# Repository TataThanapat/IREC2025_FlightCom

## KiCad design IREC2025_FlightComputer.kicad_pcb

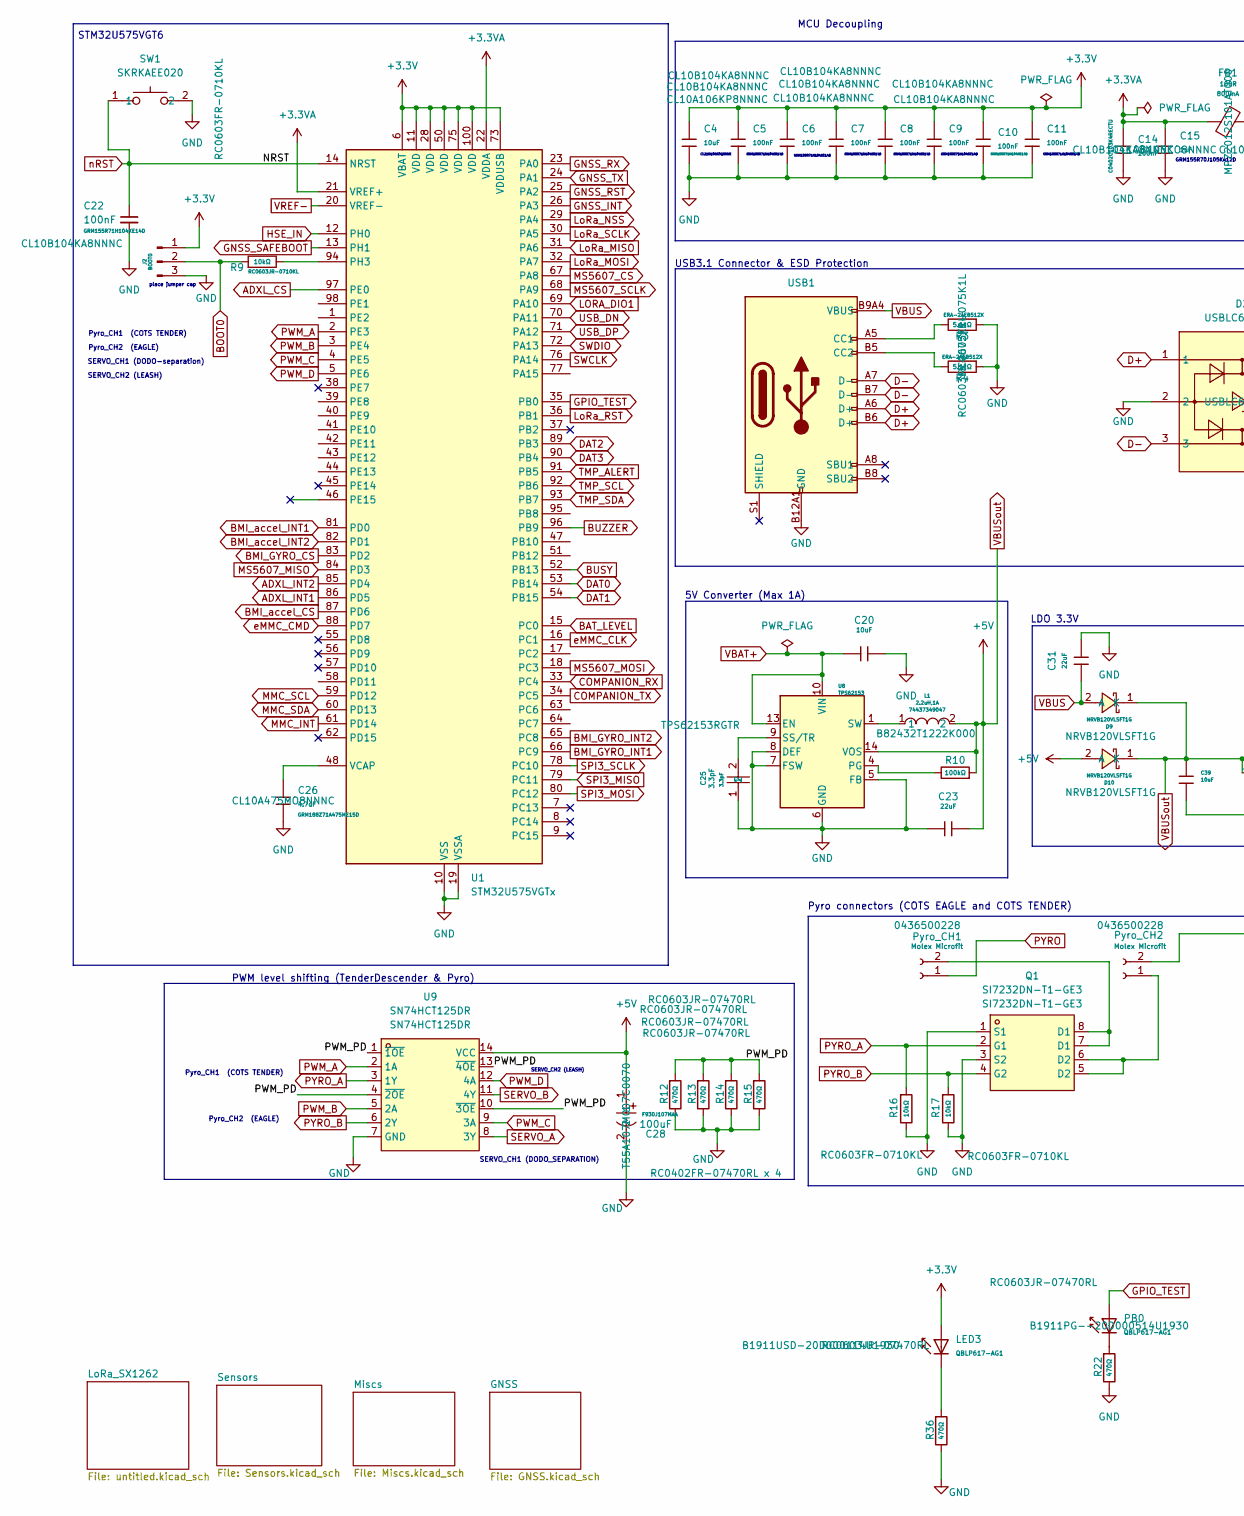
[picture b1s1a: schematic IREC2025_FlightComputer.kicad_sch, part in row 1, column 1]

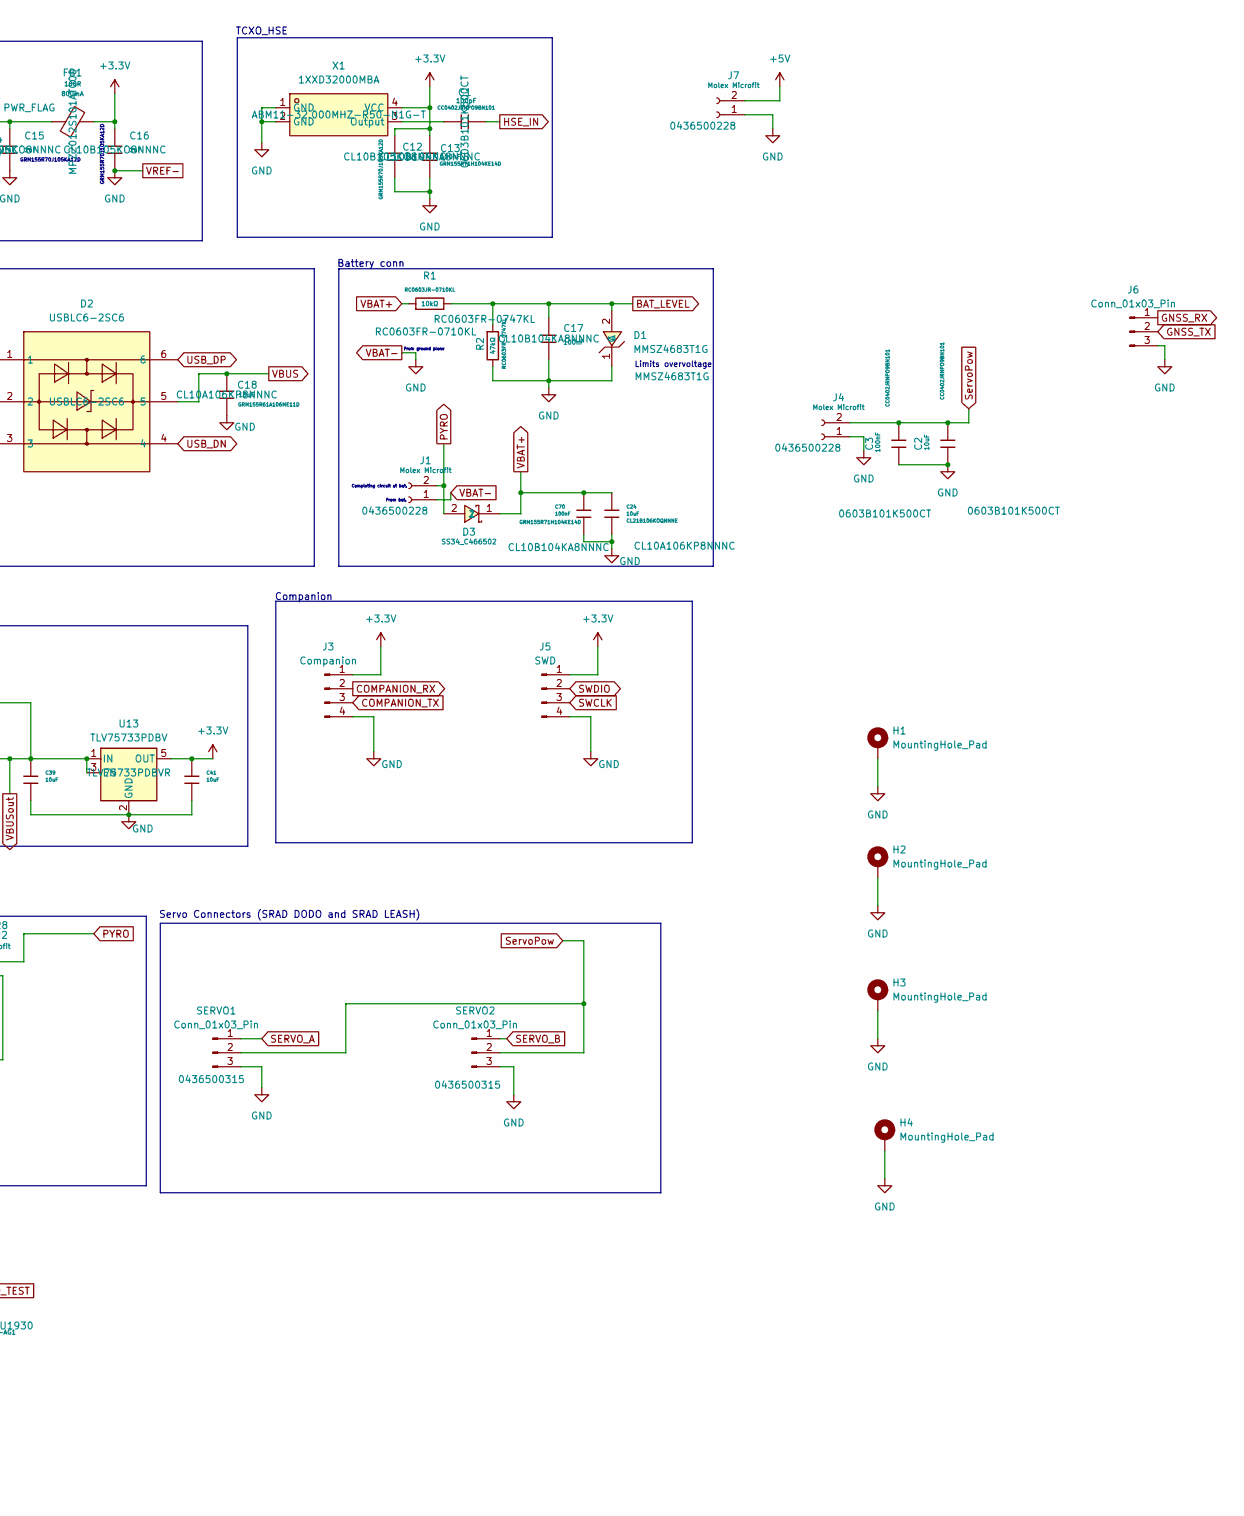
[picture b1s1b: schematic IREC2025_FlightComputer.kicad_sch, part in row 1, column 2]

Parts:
C1: 100pF; C_0603; Voltage Rated 50V; Tolerance ±5%; Part 0402CG101J500NT; LCSC C1546
C2: 10uF; C_0603; Voltage Rated 50V; Tolerance ±5%; Part 0402CG101J500NT; LCSC C1546
C3: 100nF; C_0603; Voltage Rated 50V; Tolerance ±5%; Part 0402CG101J500NT; LCSC C1546
C4, C18: 10uF; C_0603; Voltage Rated 6.3V; Tolerance ±20%; Part CL05A106MQ5NUNC; LCSC C15525
C5, C6, C7, C8, C9, C10, C11, C13, C17: 100nF; C_0603; Voltage Rated 16V; Tolerance ±10%; Part CL05B104KO5NNNC; LCSC C1525
C12, C15, C16: 1uF; C_0603; Voltage Rated 25V; Tolerance ±10%; Part CL05A105KA5NQNC; LCSC C52923
C14: 100nF; C_0603; Voltage Rated 50V; Tolerance ±10%; Part CL05B103KB5NNNC; LCSC C15195
C20: 10uF; C_0603; Voltage Rated 25V; Tolerance ±20%; Part CL10A106MA8NRNC; LCSC C96446
C22: 100nF; C_0603; Digikey Parts CL10B104KA8NNNC
C23, C31: 22uF; C_0603; Voltage Rated 6.3V; Tolerance ±20%; Part CL10A226MQ8NRNC; LCSC C59461
C24, C39, C41: 10uF; C_0603; Voltage Rated 50V; Tolerance ±10%; Part CL31A106KBHNNNE; LCSC C13585
C25: 3.3pF; C_0603; LCSC Part C76906
C26: 4.7uF; C_0603; Voltage Rated 10V; Tolerance ±20%; Part CL05A475MP5NRNC; LCSC C23733
C28: 100uF; CAP-SMD_L3.2-W1.6; LCSC Part C561794
C70: 100nF; C_0603; Voltage Rated 50V; Tolerance ±10%; Part CL31B104KBCNNNC; LCSC C24497
D1: MMSZ4683T1G; SOD-123_L2.8-W1.8-LS3.7-RD; LCSC Part C235985
D2: USBLC6-2SC6; SOT-23-6_L2.9-W1.6-P0.95-LS2.8-BL; LCSC Part C7519
D3: SS34_C466502; DIOM7959X262N; LCSC Part C466502
D9, D10: NRVB120VLSFT1G; SOD-123_L2.7-W1.6-LS3.7-RD-1; LCSC Part C604264
FB1: 100R; FB_0603; Current Rating 800mA; Tolerance ±25%; Part GZ2012D101TF; LCSC C1015
H1, H2, H3, H4: MountingHole_Pad; MountingHole_3.2mm_M3_DIN965_Pad
J1, J4, J7: Molex Microfit; Molex_Micro-Fit_3.0_43650-0215_1x02_P3.00mm_Vertical; Digikey Parts 0436500228
J2: BOOT0; PinHeader_1x03_P2.54mm_Vertical
J3: Companion; PinHeader_1x04_P2.54mm_Vertical
J5: SWD; PinHeader_1x04_P2.54mm_Vertical
J6: Conn_01x03_Pin; PinHeader_1x03_P2.54mm_Vertical
L1: 2.2uH,1A; IND_EPCOS_B82432T_EPC; LCSC Part C5156236
LED3: QBLP617-AG1; D_0603; Part KT-0603R; LCSC C2286
PB0: QBLP617-AG1; D_0603; Part KT-0603R; LCSC C2286
Pyro_CH1, Pyro_CH2: Molex Microfit; Molex_Micro-Fit_3.0_43650-0215_1x02_P3.00mm_Vertical; Digikey Parts 0436500228
Q1: SI7232DN-T1-GE3; POWER-1212-8_L3.3-W3.3-P0.66-LS3.3-BL; LCSC Part C144854
R1, R9: 10kΩ; R_0603; Overload Voltage (Max) 50V; Tolerance ±1%; Part 0402WGF1002TCE; LCSC C25744
R2: 47kΩ; R_0603; Overload Voltage (Max) 50V; Tolerance ±1%; Part 0402WGF4702TCE; LCSC C25792
R3, R4: 5.1kΩ; R_0603; Overload Voltage (Max) 50V; Tolerance ±1%; Part 0402WGF5101TCE; LCSC C25905
R10: 100kΩ; R_0603; Overload Voltage (Max) 50V; Tolerance ±1%; Part 0402WGF1003TCE; LCSC C25741
R12, R13, R14, R15, R22, R36: 470Ω; R_0603; Overload Voltage (Max) 50V; Tolerance ±1%; Part 0402WGF4700TCE; LCSC C25117
R16, R17: 10kΩ; R_0603; Overload Voltage (Max) 50V; Tolerance ±1%; Part 0402WGF3301TCE; LCSC C25890
SERVO1, SERVO2: Conn_01x03_Pin; Molex_Micro-Fit_3.0_43650-0315_1x03_P3.00mm_Vertical; Digikey Parts 0436500315
SW1: SKRKAEE020; SW-SMD_L3.9-W3.0-P4.45; LCSC Part C115357
U1: STM32U575VGTx; LQFP-100_14x14mm_P0.5mm
U8: TPS62153; VQFN-16-1EP_3x3mm_P0.5mm_EP1.68x1.68mm_ThermalVias; Digikey Parts TPS62153RGTR
U9: SN74HCT125DR; SOIC-14_L8.7-W3.9-P1.27-LS6.0-BL; LCSC Part C352957
U13: TLV75733PDBV; SOT-23-5; Digikey Parts TLV75733PDBVR
USB1: Connector, USB-TYPE-C-16P; TYPE-C-SMD_HX-TYPE-C-16PIN; LCSC C2927039
X1: 1XXD32000MBA; OSC-SMD_4P-L2.0-W1.6-BL_1XXD; LCSC Part C253694

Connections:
+3.3V: C4.1, C5.1, C6.1, C7.1, C8.1, C9.1, C10.1, C11.1, C12.1, C13.1, C16.1, C41.1, FB1.2, J2.1, J3.1, J5.1, LED3.2, U1.6 (VBAT), U1.11 (VDD), U1.28 (VDD), U1.50 (VDD), U1.73 (VDDUSB), U1.75 (VDD), U1.100 (VDD), U13.5 (OUT), X1.4 (VCC); also elsewhere on the board
+3.3VA: C14.1, C15.1, FB1.1, U1.21 (VREF+), U1.22 (VDDA)
/PWM_PD: R12.1, R13.1, R14.1, R15.1, U9.1 (~1OE), U9.4 (~2OE), U9.10 (~3OE), U9.13 (~4OE)
ADXL_CS: U1.97 (PE0); also elsewhere on the board
ADXL_INT1: U1.86 (PD5); also elsewhere on the board
ADXL_INT2: U1.85 (PD4); also elsewhere on the board
BAT_LEVEL: C17.1, D1.2 (A), R1.2, R2.1, U1.15 (PC0)
BMI_GYRO_CS: U1.83 (PD2); also elsewhere on the board
BMI_GYRO_INT1: U1.66 (PC9); also elsewhere on the board
BMI_GYRO_INT2: U1.65 (PC8); also elsewhere on the board
BMI_accel_CS: U1.87 (PD6); also elsewhere on the board
BMI_accel_INT1: U1.81 (PD0); also elsewhere on the board
BMI_accel_INT2: U1.82 (PD1); also elsewhere on the board
BOOT0: J2.2, R9.1
BUSY: U1.52 (PB13); also elsewhere on the board
BUZZER: U1.96 (PB9); also elsewhere on the board
COMPANION_RX: J3.2, U1.33 (PC4)
COMPANION_TX: J3.3, U1.34 (PC5)
D+: D2.1, USB1.A6 (D+), USB1.B6 (D+)
D-: D2.3, USB1.A7 (D-), USB1.B7 (D-)
DAT0: U1.53 (PB14); also elsewhere on the board
DAT1: U1.54 (PB15); also elsewhere on the board
DAT2: U1.89 (PB3); also elsewhere on the board
DAT3: U1.90 (PB4); also elsewhere on the board
GNSS_INT: U1.26 (PA3); also elsewhere on the board
GNSS_RST: U1.25 (PA2); also elsewhere on the board
GNSS_RX: J6.1, U1.23 (PA0); also elsewhere on the board
GNSS_SAFEBOOT: U1.13 (PH1); also elsewhere on the board
GNSS_TX: J6.2, U1.24 (PA1); also elsewhere on the board
GPIO_TEST: PB0.2, U1.35 (PB0)
HSE_IN: C1.2, U1.12 (PH0)
LORA_DIO1: U1.69 (PA10); also elsewhere on the board
LoRa_MISO: U1.31 (PA6); also elsewhere on the board
LoRa_MOSI: U1.32 (PA7); also elsewhere on the board
LoRa_NSS: U1.29 (PA4); also elsewhere on the board
LoRa_RST: U1.36 (PB1); also elsewhere on the board
LoRa_SCLK: U1.30 (PA5); also elsewhere on the board
MMC_INT: U1.61 (PD14); also elsewhere on the board
MMC_SCL: U1.59 (PD12); also elsewhere on the board
MMC_SDA: U1.60 (PD13); also elsewhere on the board
MS5607_CS: U1.67 (PA8); also elsewhere on the board
MS5607_MISO: U1.84 (PD3); also elsewhere on the board
MS5607_MOSI: U1.18 (PC3); also elsewhere on the board
MS5607_SCLK: U1.68 (PA9); also elsewhere on the board
unnamed: L1.1, U8.1 (SW), U8.2 (SW), U8.3 (SW)
unnamed: LED3.1, R36.1
unnamed: PB0.1, R22.1
unnamed: Pyro_CH1.2, Q1.7 (D1), Q1.8 (D1)
unnamed: Pyro_CH2.1, Q1.5 (D2), Q1.6 (D2)
unnamed: R9.2, U1.94 (PH3)
unnamed: C26.1, U1.48 (VCAP)
unnamed: R10.2, U8.4 (PG)
unnamed: C25.2, U8.9 (SS/TR)
unnamed: R3.2, USB1.A5 (CC1)
unnamed: R4.2, USB1.B5 (CC2)
unnamed: C1.1, X1.3 (Output)
PWM_A: U1.2 (PE3), U9.2 (1A)
PWM_B: U1.3 (PE4), U9.5 (2A)
PWM_C: U1.4 (PE5), U9.9 (3A)
PWM_D: U1.5 (PE6), U9.12 (4A)
PYRO: D3.2, J1.2, Pyro_CH1.1, Pyro_CH2.2
PYRO_A: Q1.2 (G1), R16.1, U9.3 (1Y)
PYRO_B: Q1.4 (G2), R17.1, U9.6 (2Y)
SERVO_A: SERVO1.1, U9.8 (3Y)
SERVO_B: SERVO2.1, U9.11 (4Y)
SWCLK: J5.3, U1.76 (PA14)
SWDIO: J5.2, U1.72 (PA13)
ServoPow: C2.2, C3.2, J4.2, SERVO1.2, SERVO2.2
TMP_ALERT: U1.91 (PB5); also elsewhere on the board
TMP_SCL: U1.92 (PB6); also elsewhere on the board
TMP_SDA: U1.93 (PB7); also elsewhere on the board
USB_DN: D2.4, U1.70 (PA11)
USB_DP: D2.6, U1.71 (PA12)
VBAT+: C20.1, C24.1, C70.1, D3.1, R1.1, U8.10 (VIN), U8.11 (VIN), U8.12 (VIN), U8.13 (EN)
VBAT-: C2.1, C3.1, C4.2, C5.2, C6.2, C7.2, C8.2, C9.2, C10.2, C11.2, C12.2, C13.2, C14.2, C15.2, C16.2, C17.2, C18.2, C20.2, C22.2, C23.1, C24.2, C25.1, C26.2, C28.2, C31.2, C39.2, C41.2, C70.2, D1.1 (C), D2.2, H1.1, H2.1, H3.1, H4.1, J1.1, J2.3, J3.4, J4.1, J5.4, J6.3, J7.1, Q1.1 (S1), Q1.3 (S2), R2.2, R3.1, R4.1, R12.2, R13.2, R14.2, R15.2, R16.2, R17.2, R22.2, R36.2, SERVO1.3, SERVO2.3, SW1.2, U1.10 (VSS), U1.19 (VSSA), U1.20 (VREF-), U1.27 (VSS), U1.49 (VSS), U1.74 (VSS), U1.99 (VSS), U8.5 (FB), U8.6 (GND), U8.7 (FSW), U8.8 (DEF), U8.15 (GND), U8.16 (GND), U8.17 (GND), U9.7 (GND), U13.2 (GND), USB1.A12B1 (GND), USB1.B12A1 (GND), X1.1 (GND), X1.2 (GND); also elsewhere on the board
VBUS: C18.1, C31.1, D2.5, D9.2 (A), USB1.A9B4 (VBUS), USB1.B9A4 (VBUS)
VBUSout: C23.2, C28.1, C39.1, D9.1 (K), D10.1 (K), D10.2 (A), J7.2, L1.2, R10.1, U8.14 (VOS), U9.14 (VCC), U13.1 (IN), U13.3 (EN); also elsewhere on the board
eMMC_CLK: U1.16 (PC1); also elsewhere on the board
eMMC_CMD: U1.88 (PD7); also elsewhere on the board
nRST: C22.1, SW1.1, U1.14 (NRST)

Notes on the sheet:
Pyro connectors (COTS EAGLE and COTS TENDER)
PWM level shifting (TenderDescender & Pyro)
SERVO_CH2 (LEASH)
Pyro_CH2 (EAGLE)
STM32U575VGT6
GRM155R71H104KE14D
Battery conn
Completing circuit at bat.
Pyro_CH1 (COTS TENDER)
CL21B106KOQNNNE
Limits overvoltage
SERVO_CH1 (DODO_SEPARATION)
5V Converter (Max 1A)
GRM155R70J105KA12D
Servo Connectors (SRAD DODO and SRAD LEASH)
From ground plane
place jumper cap
MCU Decoupling
SERVO_CH1 (DODO-separation)
LDO 3.3V
From bat.
TCXO_HSE
USB3.1 Connector & ESD Protection
Companion

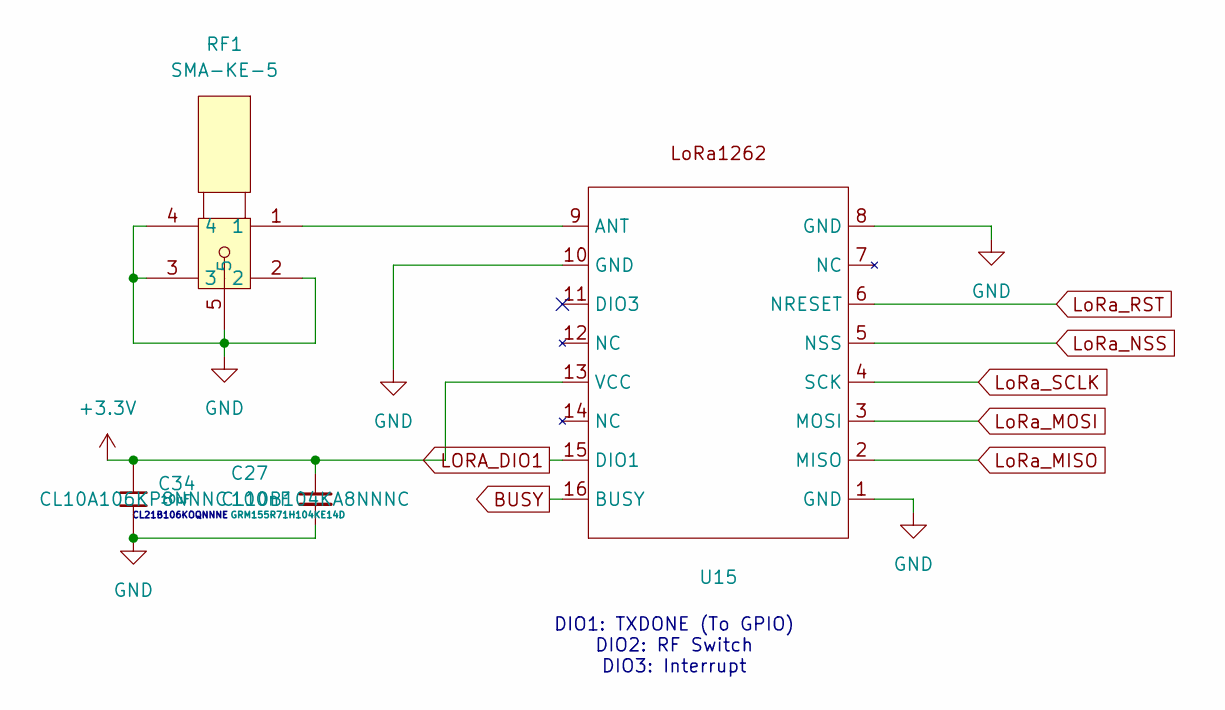
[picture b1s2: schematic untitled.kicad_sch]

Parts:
C27: 100nF; C_0603; Digikey Parts CL10B104KA8NNNC
C34: 10uF; C_0603; Voltage Rated 6.3V; Tolerance ±20%; Part CL05A106MQ5NUNC; LCSC C15525
RF1: SMA-KE-5; SMA-TH_SMA-KHDB_C9900020423; LCSC Part C20415804
U15: G-NiceRF LoRa1262-915

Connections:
+3.3V: C27.1, C34.1, U15.13 (VCC); also elsewhere on the board
BUSY: U15.16 (BUSY); also elsewhere on the board
LORA_DIO1: U15.15 (DIO1); also elsewhere on the board
LoRa_MISO: U15.2 (MISO); also elsewhere on the board
LoRa_MOSI: U15.3 (MOSI); also elsewhere on the board
LoRa_NSS: U15.5 (NSS); also elsewhere on the board
LoRa_RST: U15.6 (NRESET); also elsewhere on the board
LoRa_SCLK: U15.4 (SCK); also elsewhere on the board
unnamed: RF1.1, U15.9 (ANT)
VBAT-: C27.2, C34.2, RF1.2, RF1.3, RF1.4, RF1.5, U15.1 (GND), U15.8 (GND), U15.10 (GND); also elsewhere on the board

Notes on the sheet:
DIO1: TXDONE (To GPIO) DIO2: RF Switch DIO3: Interrupt
CL21B106KOQNNNE

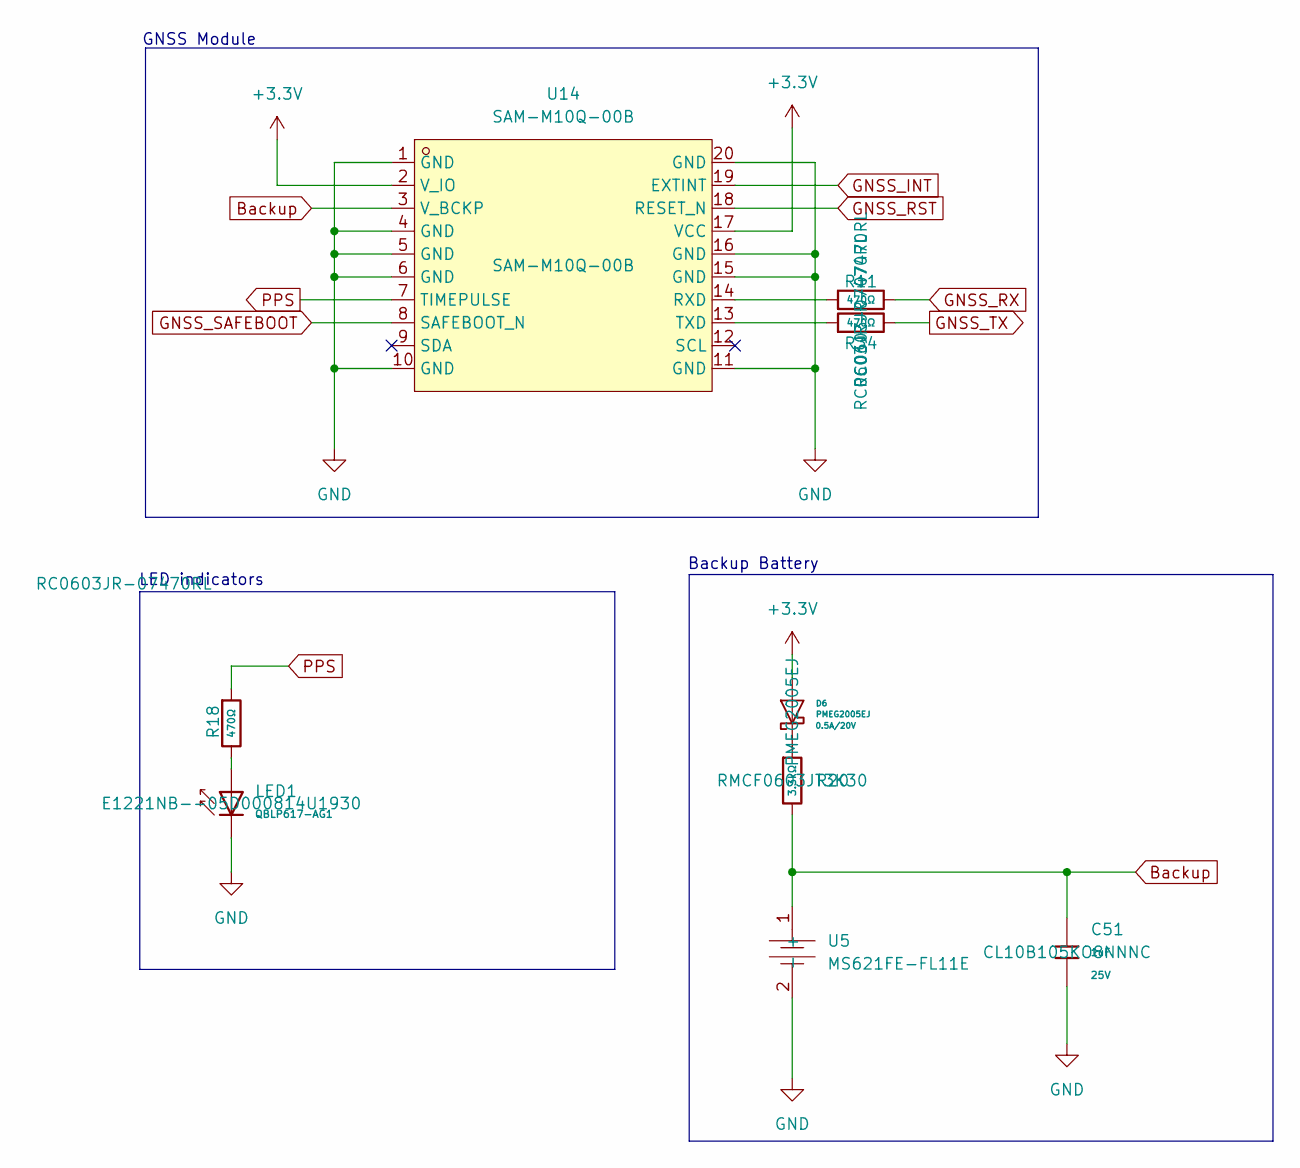
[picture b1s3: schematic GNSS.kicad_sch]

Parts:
C51: 1uF; C_0603; Voltage Rated 25V; Tolerance ±10%; Part CL05A105KA5NQNC; LCSC C52923
D6: PMEG2005EJ; D_SOD-323F; Ratings 0.5A/20V; Digikey Parts PMEG2005EJ
LED1: QBLP617-AG1; D_0603; Part KT-0603R; LCSC C2286
R11, R18, R34: 470Ω; R_0603; Overload Voltage (Max) 50V; Tolerance ±1%; Part 0402WGF4700TCE; LCSC C25117
R20: 3.3kΩ; R_0603; Overload Voltage (Max) 50V; Tolerance ±1%; Part 0402WGF3301TCE; LCSC C25890
U5: MS621FE-FL11E; BAT-SMD_FL11E; LCSC Part C80909
U14: SAM-M10Q-00B; LCC-20_L15.5-W15.5-P1.90_SAM-M10Q-00B; LCSC Part C5443880

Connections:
+3.3V: D6.2 (A), U14.2 (V_IO), U14.17 (VCC); also elsewhere on the board
Backup: C51.1, R20.2, U5.1 (+), U14.3 (V_BCKP)
GNSS_INT: U14.19 (EXTINT); also elsewhere on the board
GNSS_RST: U14.18 (RESET_N); also elsewhere on the board
GNSS_RX: R11.2; also elsewhere on the board
GNSS_SAFEBOOT: U14.8 (SAFEBOOT_N); also elsewhere on the board
GNSS_TX: R34.2; also elsewhere on the board
unnamed: D6.1 (K), R20.1
unnamed: LED1.2, R18.2
unnamed: R11.1, U14.14 (RXD)
unnamed: R34.1, U14.13 (TXD)
PPS: R18.1, U14.7 (TIMEPULSE)
VBAT-: C51.2, LED1.1, U5.2 (-), U14.1 (GND), U14.4 (GND), U14.5 (GND), U14.6 (GND), U14.10 (GND), U14.11 (GND), U14.15 (GND), U14.16 (GND), U14.20 (GND); also elsewhere on the board

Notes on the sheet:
GNSS Module
LED indicators
Backup Battery

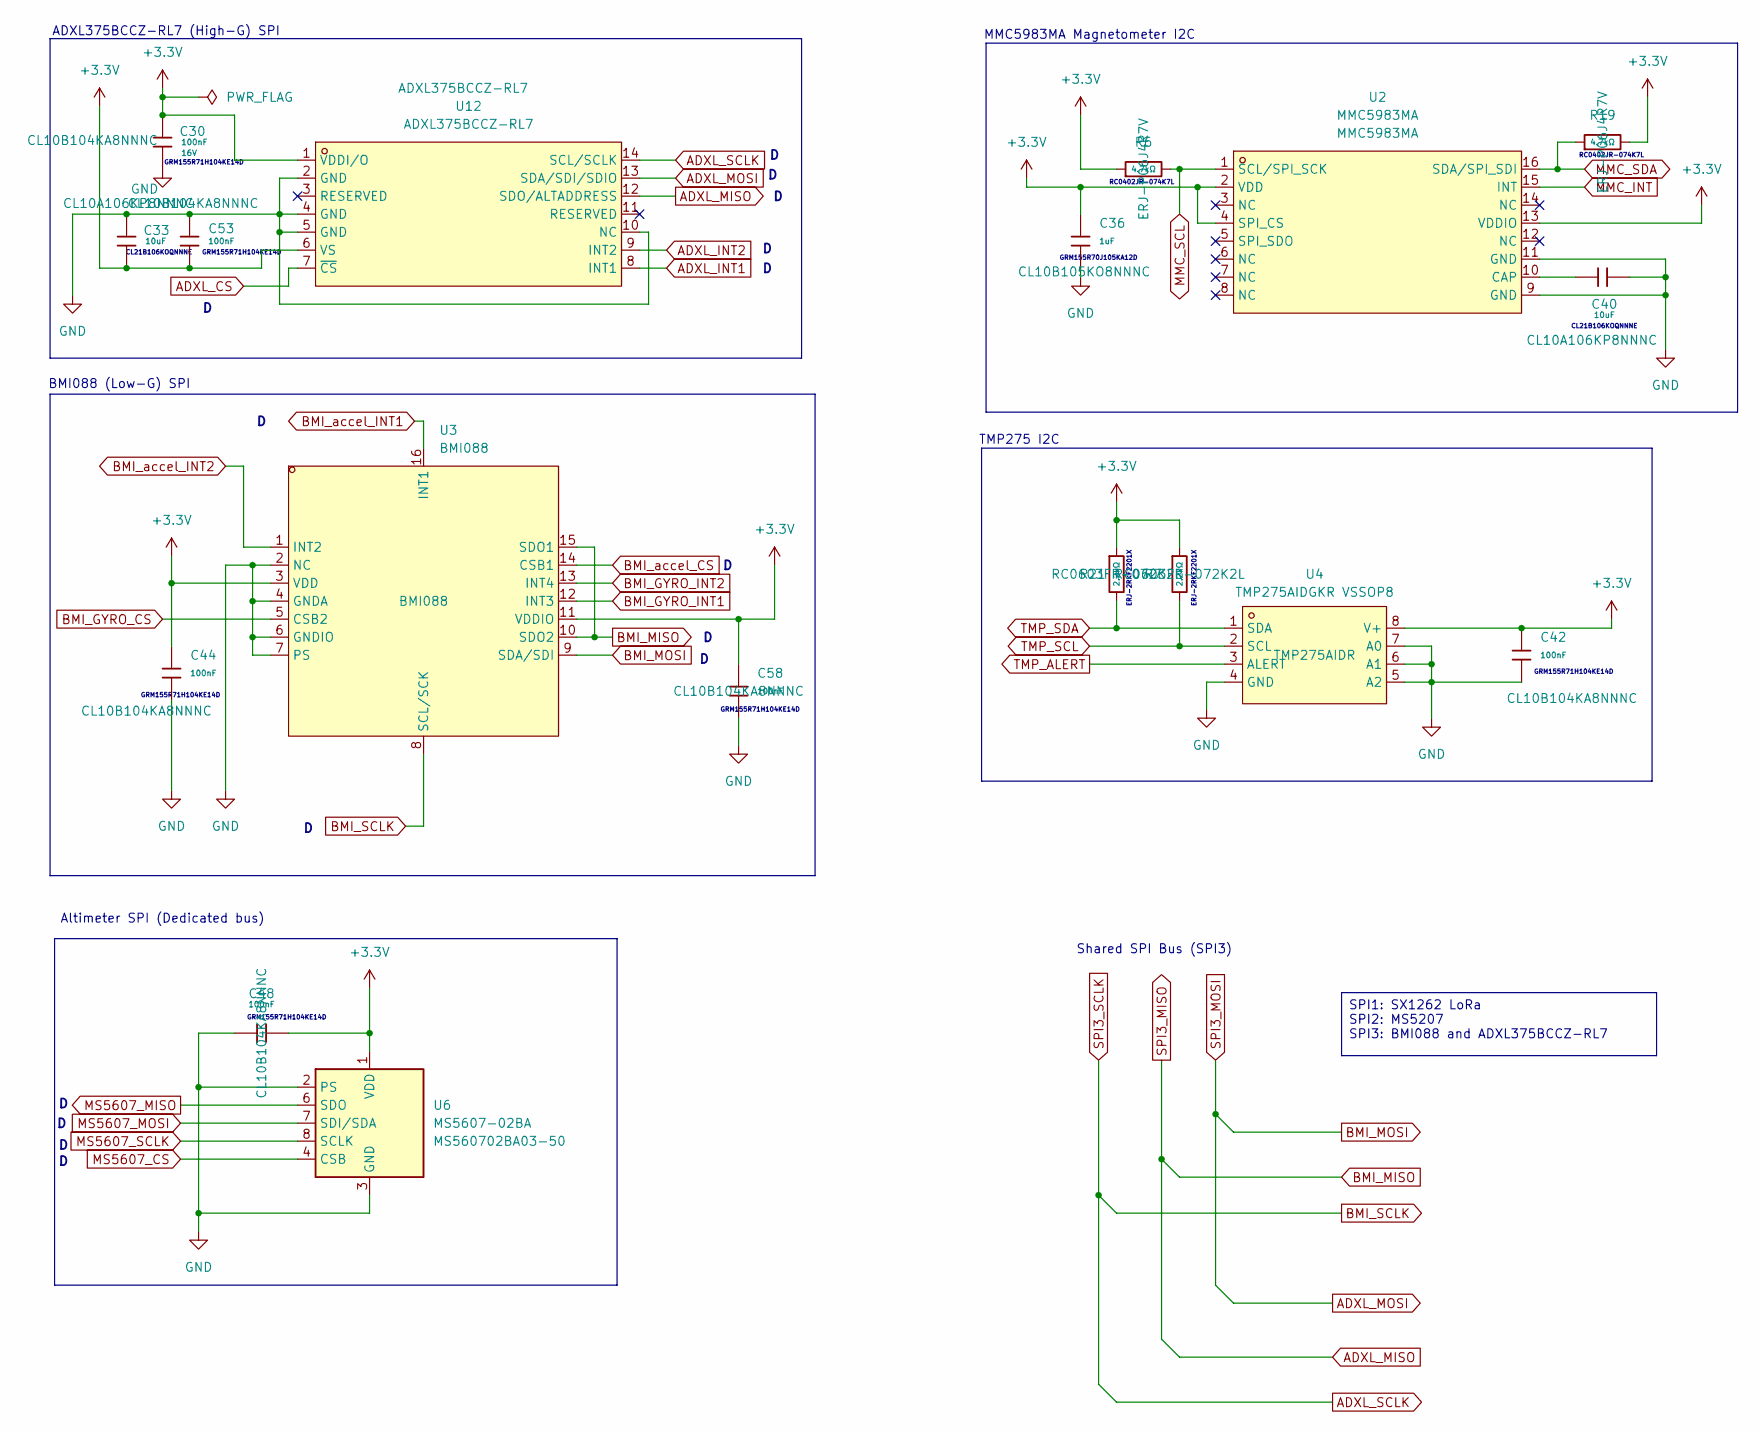
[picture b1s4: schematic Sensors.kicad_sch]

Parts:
C30, C42, C44, C48, C53, C58: 100nF; C_0603; Voltage Rated 16V; Tolerance ±10%; Part CL05B104KO5NNNC; LCSC C1525
C33, C40: 10uF; C_0603; Voltage Rated 6.3V; Tolerance ±20%; Part CL05A106MQ5NUNC; LCSC C15525
C36: 1uF; C_0603; Voltage Rated 25V; Tolerance ±10%; Part CL05A105KA5NQNC; LCSC C52923
R6, R19: 4.7kΩ; R_0603; Overload Voltage (Max) 50V; Tolerance ±1%; Part 0402WGF4701TCE; LCSC C25900
R7, R21: 2.2kΩ; R_0603; Overload Voltage (Max) 50V; Tolerance ±1%; Part 0402WGF2201TCE; LCSC C25879
U2: MMC5983MA; LGA-16_L3.0-W3.0-P0.50-BL_SQ; LCSC Part C404329
U3: BMI088; LGA-16_L4.5-W3.0-P0.50-BL; LCSC Part C194919
U4: TMP275AIDGKR VSSOP8; VSSOP-8_L3.0-W3.0-P0.65-LS5.0-BL; LCSC Part C87815
U6: MS5607-02BA; LGA-8_3x5mm_P1.25mm; Digikey Parts MS560702BA03-50
U12: ADXL375BCCZ-RL7; LGA-14_L5.0-W3.0-P0.80-BL; LCSC Part C481898

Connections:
+3.3V: C30.1, C33.2, C36.1, C42.1, C44.1, C48.2, C53.2, C58.1, R6.1, R7.1, R19.2, R21.1, U2.2 (VDD), U2.4 (SPI_CS), U2.13 (VDDIO), U3.3 (VDD), U3.11 (VDDIO), U4.8 (V+), U6.1 (VDD), U12.1 (VDDI/O), U12.6 (VS); also elsewhere on the board
ADXL_CS: U12.7 (~CS); also elsewhere on the board
ADXL_INT1: U12.8 (INT1); also elsewhere on the board
ADXL_INT2: U12.9 (INT2); also elsewhere on the board
BMI_GYRO_CS: U3.5 (CSB2); also elsewhere on the board
BMI_GYRO_INT1: U3.12 (INT3); also elsewhere on the board
BMI_GYRO_INT2: U3.13 (INT4); also elsewhere on the board
BMI_accel_CS: U3.14 (CSB1); also elsewhere on the board
BMI_accel_INT1: U3.16 (INT1); also elsewhere on the board
BMI_accel_INT2: U3.1 (INT2); also elsewhere on the board
MMC_INT: U2.15 (INT); also elsewhere on the board
MMC_SCL: R6.2, U2.1 (SCL/SPI_SCK); also elsewhere on the board
MMC_SDA: R19.1, U2.16 (SDA/SPI_SDI); also elsewhere on the board
MS5607_CS: U6.4 (CSB), U6.5 (CSB); also elsewhere on the board
MS5607_MISO: U6.6 (SDO); also elsewhere on the board
MS5607_MOSI: U6.7 (SDI/SDA); also elsewhere on the board
MS5607_SCLK: U6.8 (SCLK); also elsewhere on the board
unnamed: C40.1, U2.10 (CAP)
TMP_ALERT: U4.3 (ALERT); also elsewhere on the board
TMP_SCL: R7.2, U4.2 (SCL); also elsewhere on the board
TMP_SDA: R21.2, U4.1 (SDA); also elsewhere on the board
VBAT-: C30.2, C33.1, C36.2, C40.2, C42.2, C44.2, C48.1, C53.1, C58.2, U2.9 (GND), U2.11 (GND), U3.2 (NC), U3.4 (GNDA), U3.6 (GNDIO), U3.7 (PS), U4.4 (GND), U4.5 (A2), U4.6 (A1), U4.7 (A0), U6.2 (PS), U6.3 (GND), U12.2 (GND), U12.4 (GND), U12.5 (GND), U12.10 (NC); also elsewhere on the board

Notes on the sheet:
Shared SPI Bus (SPI3)
ERJ-2RKF2201X
CL21B106KOQNNNE
GRM155R71H104KE14D
RC0402JR-074K7L
GRM155R70J105KA12D
TMP275 I2C
BMI088 (Low-G) SPI
MMC5983MA Magnetometer I2C
ADXL375BCCZ-RL7 (High-G) SPI
Altimeter SPI (Dedicated bus)
SPI1: SX1262 LoRa SPI2: MS5207 SPI3: BMI088 and ADXL375BCCZ-RL7

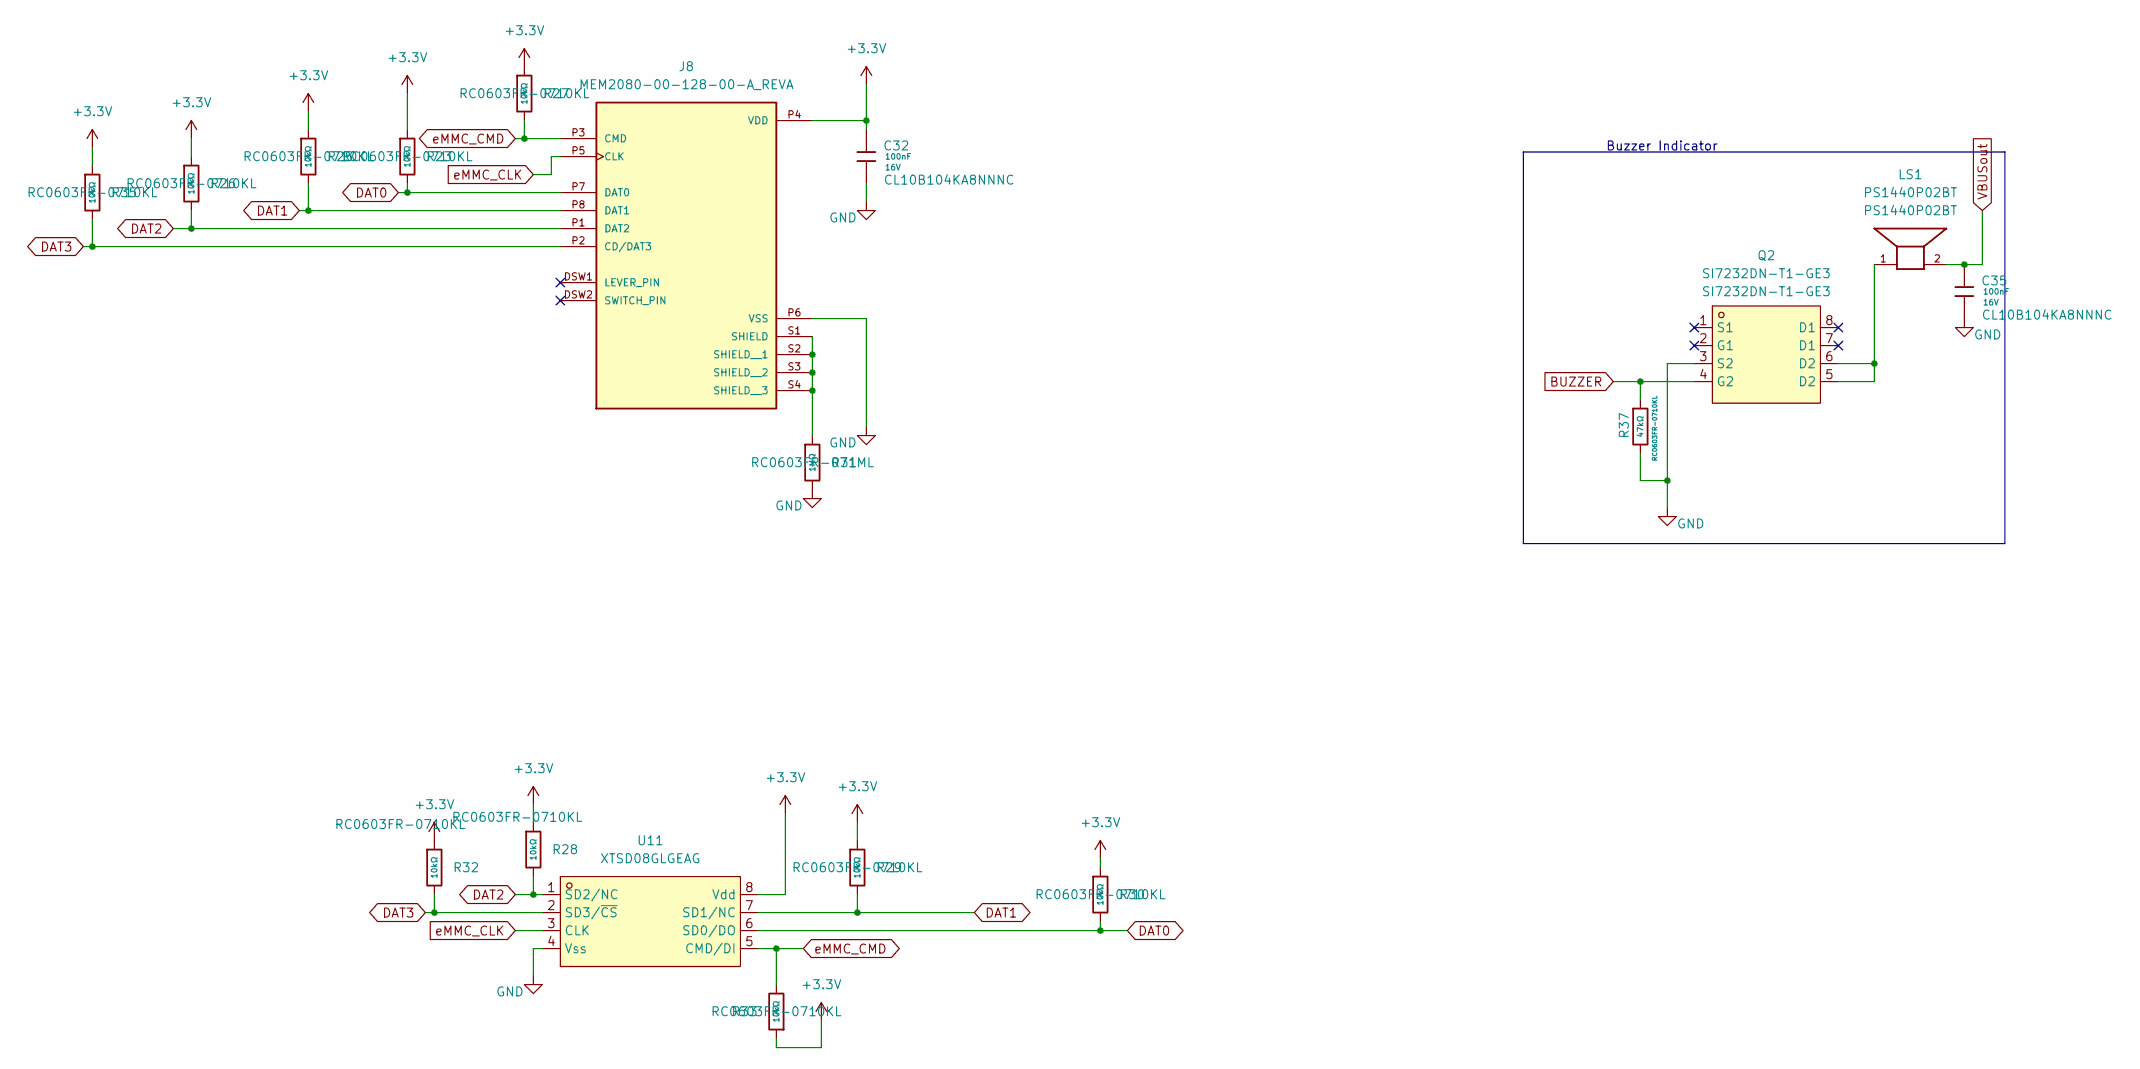
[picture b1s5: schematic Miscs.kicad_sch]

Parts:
C32, C35: 100nF; C_0603; Voltage Rated 16V; Tolerance ±10%; Part CL05B104KO5NNNC; LCSC C1525
J8: MEM2080-00-128-00-A_REVA; GCT_MEM2080-00-128-00-A_REVA; PARTREV A; Digikey Parts MEM2080-00-128-00-A
LS1: PS1440P02BT; PS1440P02BT_BUZZER_PS1440P02BT; Digikey Parts PS1440P02BT
Q2: SI7232DN-T1-GE3; POWER-1212-8_L3.3-W3.3-P0.66-LS3.3-BL; LCSC Part C144854
R23, R25, R26, R27, R28, R29, R30, R32, R33, R35: 10kΩ; R_0603; Overload Voltage (Max) 75V; Tolerance ±1%; Part 0603WAF1002T5E; LCSC C25804
R31: 1MΩ; R_0603; Overload Voltage (Max) 75V; Tolerance ±1%; Part 0603WAF1004T5E; LCSC C22935
R37: 47kΩ; R_0603; Overload Voltage (Max) 50V; Tolerance ±1%; Part 0402WGF3301TCE; LCSC C25890
U11: XTSD08GLGEAG; LGA-8_L6.0-W8.0-P1.27-BL; LCSC Part C558840

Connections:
+3.3V: C32.1, J8.P4 (VDD), R23.1, R25.1, R26.1, R27.1, R28.1, R29.1, R30.1, R32.1, R33.1, R35.1, U11.8 (Vdd); also elsewhere on the board
BUZZER: Q2.4 (G2), R37.1; also elsewhere on the board
DAT0: J8.P7 (DAT0), R23.2, R30.2, U11.6 (SD0/DO); also elsewhere on the board
DAT1: J8.P8 (DAT1), R25.2, R29.2, U11.7 (SD1/NC); also elsewhere on the board
DAT2: J8.P1 (DAT2), R26.2, R28.2, U11.1 (SD2/NC); also elsewhere on the board
DAT3: J8.P2 (CD/DAT3), R32.2, R35.2, U11.2 (SD3/~CS); also elsewhere on the board
unnamed: J8.S1 (SHIELD), J8.S2 (SHIELD__1), J8.S3 (SHIELD__2), J8.S4 (SHIELD__3), R31.1
unnamed: LS1.1, Q2.5 (D2), Q2.6 (D2)
VBAT-: C32.2, C35.2, J8.P6 (VSS), Q2.3 (S2), R31.2, R37.2, U11.4 (Vss); also elsewhere on the board
VBUSout: C35.1, LS1.2; also elsewhere on the board
eMMC_CLK: J8.P5 (CLK), U11.3 (CLK); also elsewhere on the board
eMMC_CMD: J8.P3 (CMD), R27.2, R33.2, U11.5 (CMD/DI); also elsewhere on the board

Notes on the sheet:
Buzzer Indicator

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
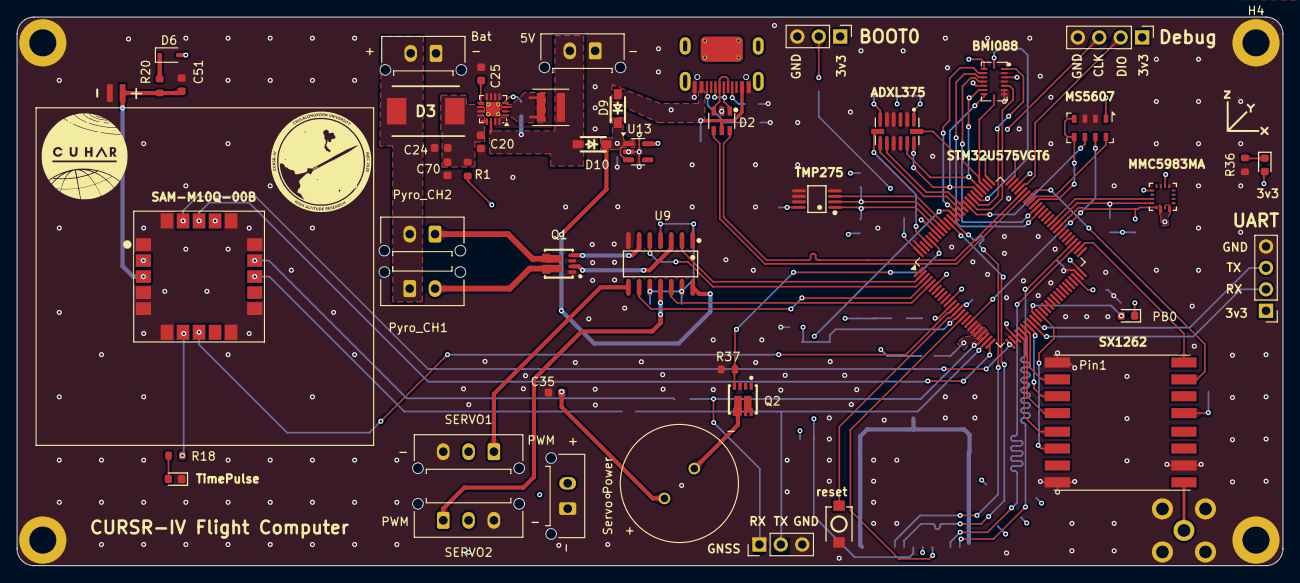
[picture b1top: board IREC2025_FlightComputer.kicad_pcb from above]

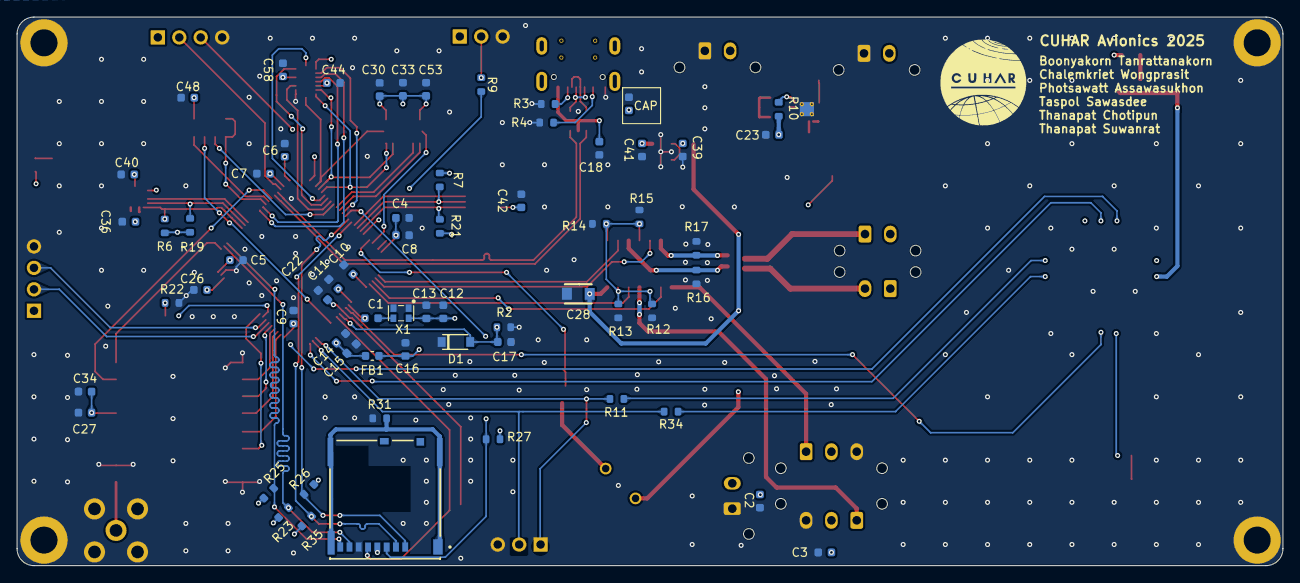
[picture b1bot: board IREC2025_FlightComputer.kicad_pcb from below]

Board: 4 copper layers, 150.0 x 65.0 mm, 119 parts (65 on the bottom side), 93 nets.

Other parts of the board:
LOGO: LOGO; CUHARLOGOMOD
LOGO#2: LOGO; CUHARLOGOMOD
